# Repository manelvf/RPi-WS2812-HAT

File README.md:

# RPi-WS2812-HAT
WS2812B intelligent RGB-LED 8x8 Matrix HAT (Hardware Attached on Top) for Raspberry Pi.

## Shop
* [RPi-WS2812-HAT](http://www.watterott.com/en/RPi-WS2812-HAT)

## Features
* 64 WS2812 RGB-LED with built-in controller with serial interface
* Atmel ATtiny85 with [Micronucleus](https://github.com/micronucleus/micronucleus) USB Bootloader
* MicroUSB connector
* ID EEPROM
* [Raspberry Pi HAT](https://github.com/raspberrypi/hats) compatible

## Hardware and Software
* [Schematics + Layout](https://github.com/watterott/RPi-WS2812-HAT/tree/master/pcb)
* [Arduino and Raspberry Pi Examples](https://github.com/watterott/RPi-WS2812-HAT/tree/master/src)
* [Little Wire](http://littlewire.cc) can also be used on the ATtiny85.
* [FAQ (Frequently Asked Questions)](https://github.com/watterott/RPi-WS2812-HAT/blob/master/docu/FAQ.md)

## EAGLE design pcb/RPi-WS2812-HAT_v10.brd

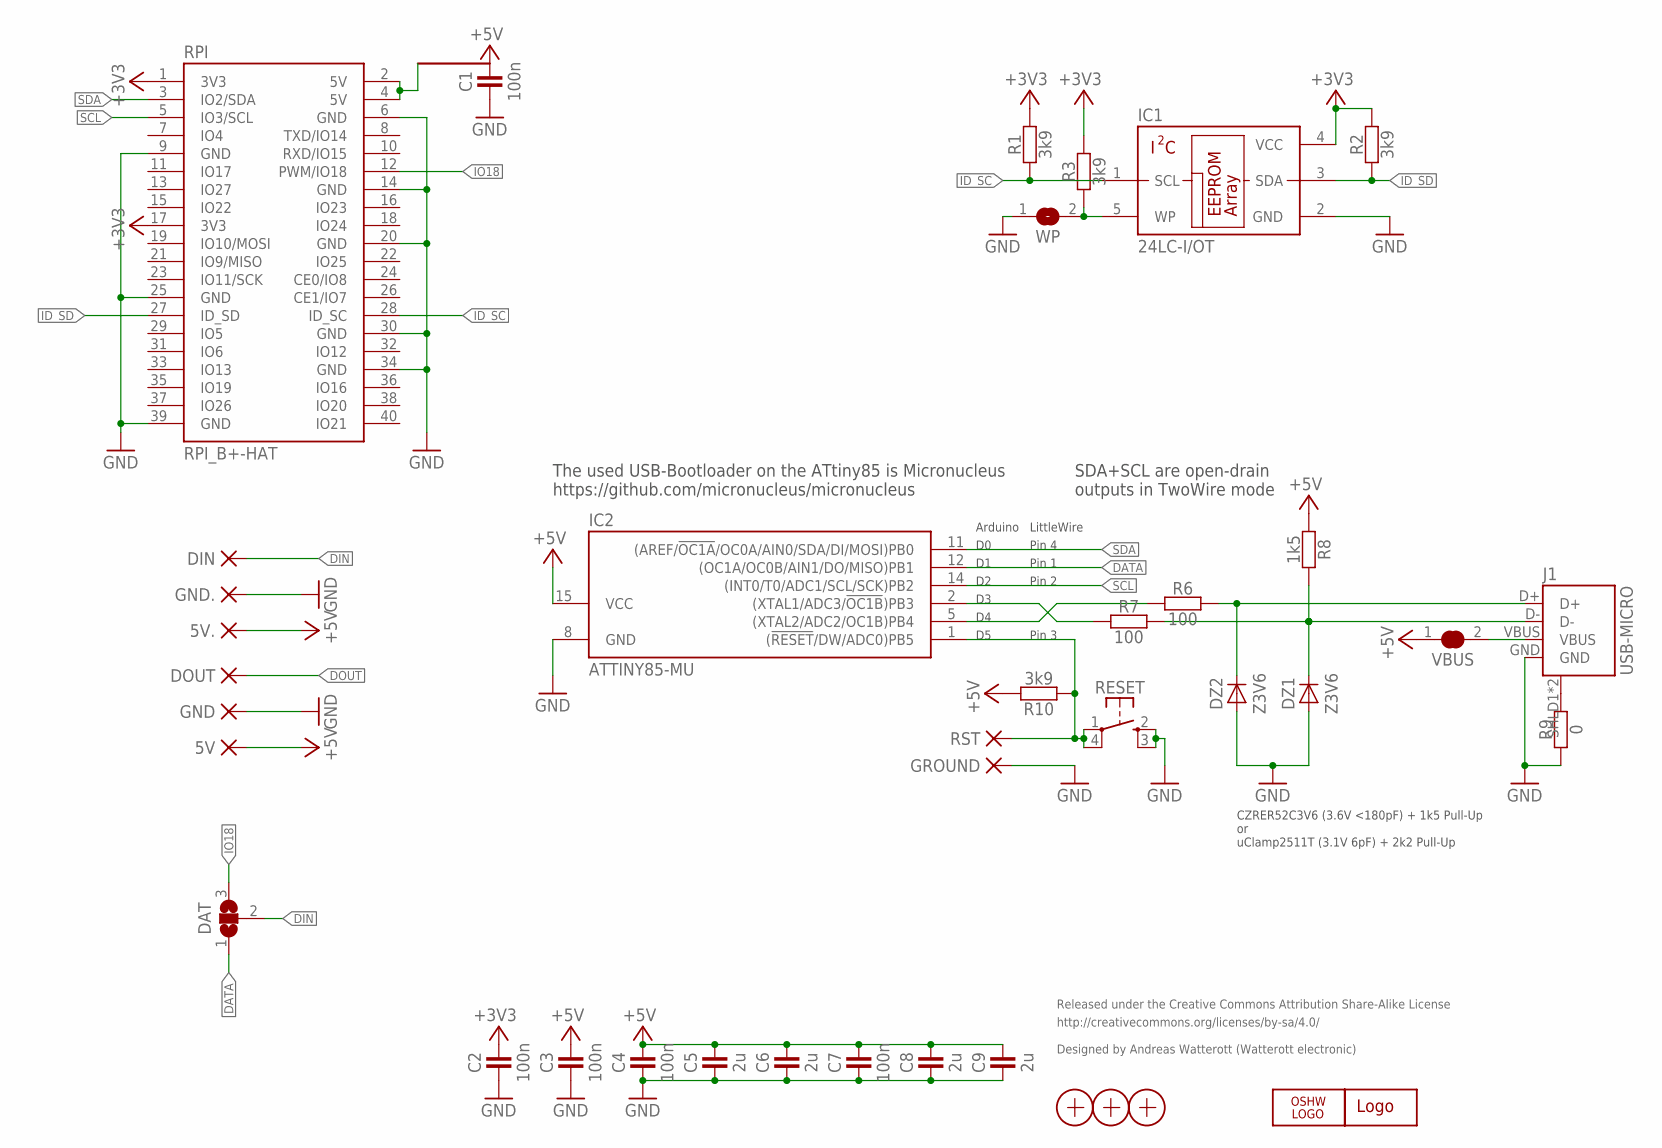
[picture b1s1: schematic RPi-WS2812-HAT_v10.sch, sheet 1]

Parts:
5V, 5V.: PAD-1.27X2.54_NC
C1, C2, C3, C4, C7: 100n; R0402
C5, C6, C8, C9: 2u; R0402
DAT: JUMPER3-0603
DIN: PAD-1.27X2.54_NC
DOUT: PAD-1.27X2.54_NC
DZ1, DZ2: Z3V6; SOD882
GND, GND.: PAD-1.27X2.54_NC
GROUND: PAD-1.27X1.27_NC
IC1: 24LC-I/OT; SOT23-5
IC2: ATTINY85-MU; QFN20-PAD
J1: USB-MICRO; USB-MICRO-10103594
LOGO1: LOGO-S_PLACE_S; SPARK_TPLACE_S
LOGO2: OSHW_LOGOX0070; OSHW_6X70
R1, R2, R3, R10: 3k9; R0402
R6, R7: 100; R0402
R8: 1k5; R0402
R9: 0; R0402
RESET: SW-TACTILE-TL3315; SW_TL3315N
RPI: RPI_B+-HAT; RPI-B+HAT
RST: PAD-1.27X1.27_NC
VBUS: JUMPER2-0603-NC; JUMPER2-0603_NC
WP: JUMPER2-0603-NC; JUMPER2-0603_NC
X1, X2, X3: PASSER-07; PASSER_07MM

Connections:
5V: RPI.2 (5V), RPI.4 (5V)
+3V3: C2.2, IC1.4 (VCC), R1.2, R2.2, R3.2, RPI.1 (3V3), RPI.17 (3V3)
+5V: 5V.1, 5V..1, C1.2, C3.2, C4.2, C5.2, C6.2, C7.2, C8.2, C9.2, IC2.15 (VCC), R8.1, R10.2, VBUS.1; also elsewhere on the board
D2_N: IC2.2 ((XTAL1/ADC3/!OC1B!)PB3), R7.1
D2_P: IC2.5 ((XTAL2/ADC2/OC1B)PB4), R6.1
DATA: DAT.1, IC2.12 ((OC1A/OC0B/AIN1/DO/MISO)PB1)
DIN: DAT.2, DIN.1; also elsewhere on the board
DOUT: DOUT.1; also elsewhere on the board
D_N: DZ1.C, J1.D-, R7.2, R8.2
D_P: DZ2.C, J1.D+, R6.2
GND: C1.1, C2.1, C3.1, C4.1, C5.1, C6.1, C7.1, C8.1, C9.1, DZ1.A, DZ2.A, GND.1, GND..1, GROUND.1, IC1.2 (GND), IC2.8 (GND), J1.GND, R9.1, RESET.2 (S1), RESET.3 (S2), RPI.6 (GND), RPI.9 (GND), RPI.14 (GND), RPI.20 (GND), RPI.25 (GND), RPI.30 (GND), RPI.34 (GND), RPI.39 (GND), WP.1; also elsewhere on the board
ID_SC: IC1.1 (SCL), R1.1, RPI.28 (ID_SC)
ID_SD: IC1.3 (SDA), R2.1, RPI.27 (ID_SD)
IO18: DAT.3, RPI.12 (PWM/IO18)
unnamed: J1.SHLD1 (SHIELD), J1.SHLD2 (SHIELD), R9.2
RST: IC2.1 ((!RESET!/DW/ADC0)PB5), R10.1, RESET.1, RESET.4 (P2), RST.1
SCL: IC2.14 ((INT0/T0/ADC1/SCL/SCK)PB2), RPI.5 (IO3/SCL)
SDA: IC2.11 ((AREF/!OC1A!/OC0A/AIN0/SDA/DI/MOSI)PB0), RPI.3 (IO2/SDA)
VBUS: J1.VBUS, VBUS.2
WP: IC1.5 (WP), R3.1, WP.2

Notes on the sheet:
Released under the Creative Commons Attribution Share-Alike License
http://creativecommons.org/licenses/by-sa/4.0/
Designed by Andreas Watterott (Watterott electronic)
The used USB-Bootloader on the ATtiny85 is Micronucleus https://github.com/micronucleus/micronucleus
CZRER52C3V6 (3.6V <180pF) + 1k5 Pull-Up or uClamp2511T (3.1V 6pF) + 2k2 Pull-Up
Pin 1
Pin 4
Pin 2
Pin 3
LittleWire
Arduino
SDA+SCL are open-drain outputs in TwoWire mode

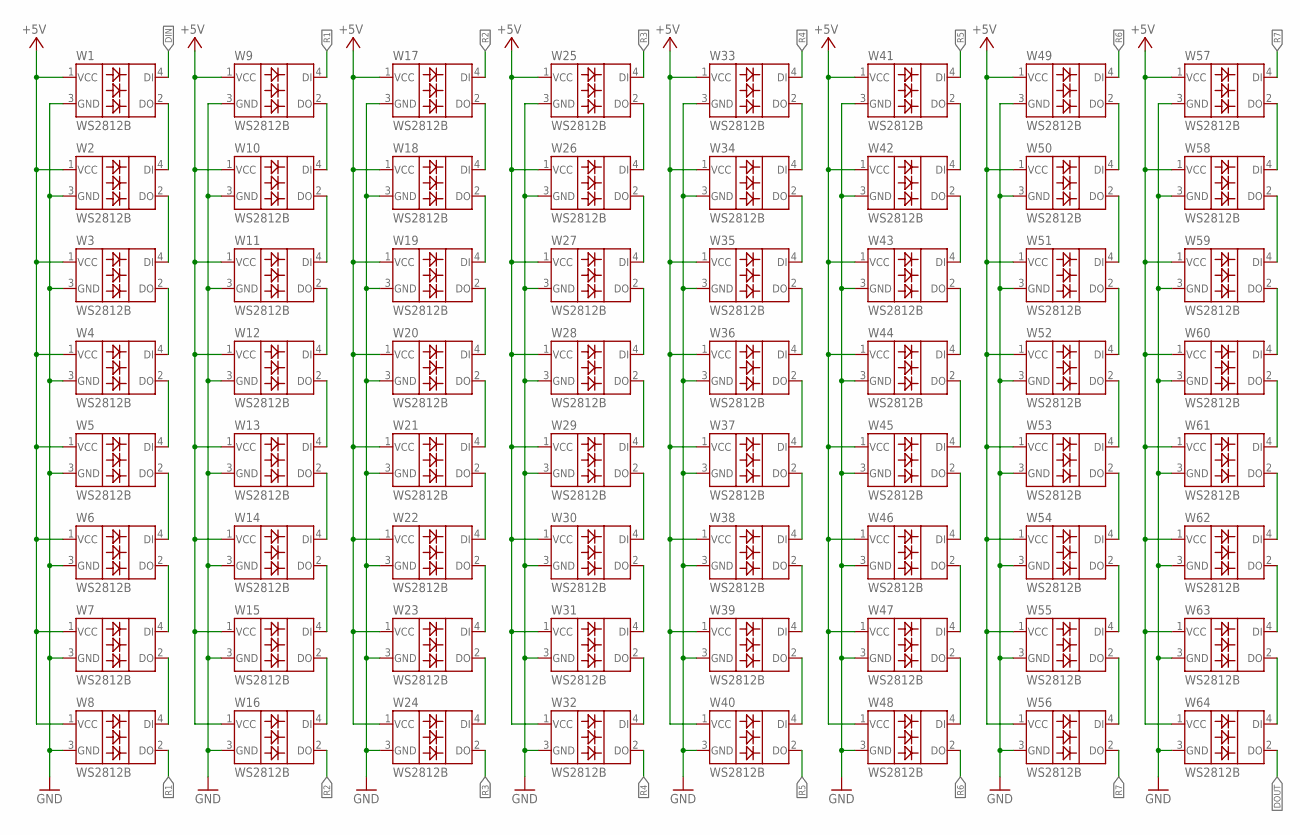
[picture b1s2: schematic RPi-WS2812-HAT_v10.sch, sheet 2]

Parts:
W1, W2, W3, W4, W5, W6, W7, W8, W9, W10, W11, W12, W13, W14, W15, W16, W17, W18, W19, W20, W21, W22, W23, W24, W25, W26, W27, W28, W29, W30, W31, W32, W33, W34, W35, W36, W37, W38, W39, W40, W41, W42, W43, W44, W45, W46, W47, W48, W49, W50, W51, W52, W53, W54, W55, W56, W57, W58, W59, W60, W61, W62, W63, W64: WS2812B

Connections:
+5V: W1.1 (VCC), W2.1 (VCC), W3.1 (VCC), W4.1 (VCC), W5.1 (VCC), W6.1 (VCC), W7.1 (VCC), W8.1 (VCC), W9.1 (VCC), W10.1 (VCC), W11.1 (VCC), W12.1 (VCC), W13.1 (VCC), W14.1 (VCC), W15.1 (VCC), W16.1 (VCC), W17.1 (VCC), W18.1 (VCC), W19.1 (VCC), W20.1 (VCC), W21.1 (VCC), W22.1 (VCC), W23.1 (VCC), W24.1 (VCC), W25.1 (VCC), W26.1 (VCC), W27.1 (VCC), W28.1 (VCC), W29.1 (VCC), W30.1 (VCC), W31.1 (VCC), W32.1 (VCC), W33.1 (VCC), W34.1 (VCC), W35.1 (VCC), W36.1 (VCC), W37.1 (VCC), W38.1 (VCC), W39.1 (VCC), W40.1 (VCC), W41.1 (VCC), W42.1 (VCC), W43.1 (VCC), W44.1 (VCC), W45.1 (VCC), W46.1 (VCC), W47.1 (VCC), W48.1 (VCC), W49.1 (VCC), W50.1 (VCC), W51.1 (VCC), W52.1 (VCC), W53.1 (VCC), W54.1 (VCC), W55.1 (VCC), W56.1 (VCC), W57.1 (VCC), W58.1 (VCC), W59.1 (VCC), W60.1 (VCC), W61.1 (VCC), W62.1 (VCC), W63.1 (VCC), W64.1 (VCC); also elsewhere on the board
DIN: W1.4 (DI); also elsewhere on the board
DOUT: W64.2 (DO); also elsewhere on the board
GND: W1.3 (GND), W2.3 (GND), W3.3 (GND), W4.3 (GND), W5.3 (GND), W6.3 (GND), W7.3 (GND), W8.3 (GND), W9.3 (GND), W10.3 (GND), W11.3 (GND), W12.3 (GND), W13.3 (GND), W14.3 (GND), W15.3 (GND), W16.3 (GND), W17.3 (GND), W18.3 (GND), W19.3 (GND), W20.3 (GND), W21.3 (GND), W22.3 (GND), W23.3 (GND), W24.3 (GND), W25.3 (GND), W26.3 (GND), W27.3 (GND), W28.3 (GND), W29.3 (GND), W30.3 (GND), W31.3 (GND), W32.3 (GND), W33.3 (GND), W34.3 (GND), W35.3 (GND), W36.3 (GND), W37.3 (GND), W38.3 (GND), W39.3 (GND), W40.3 (GND), W41.3 (GND), W42.3 (GND), W43.3 (GND), W44.3 (GND), W45.3 (GND), W46.3 (GND), W47.3 (GND), W48.3 (GND), W49.3 (GND), W50.3 (GND), W51.3 (GND), W52.3 (GND), W53.3 (GND), W54.3 (GND), W55.3 (GND), W56.3 (GND), W57.3 (GND), W58.3 (GND), W59.3 (GND), W60.3 (GND), W61.3 (GND), W62.3 (GND), W63.3 (GND), W64.3 (GND); also elsewhere on the board
unnamed: W1.2 (DO), W2.4 (DI)
unnamed: W2.2 (DO), W3.4 (DI)
unnamed: W3.2 (DO), W4.4 (DI)
unnamed: W4.2 (DO), W5.4 (DI)
unnamed: W5.2 (DO), W6.4 (DI)
unnamed: W6.2 (DO), W7.4 (DI)
unnamed: W7.2 (DO), W8.4 (DI)
unnamed: W9.2 (DO), W10.4 (DI)
unnamed: W10.2 (DO), W11.4 (DI)
unnamed: W11.2 (DO), W12.4 (DI)
unnamed: W12.2 (DO), W13.4 (DI)
unnamed: W13.2 (DO), W14.4 (DI)
unnamed: W15.2 (DO), W16.4 (DI)
unnamed: W14.2 (DO), W15.4 (DI)
unnamed: W23.2 (DO), W24.4 (DI)
unnamed: W22.2 (DO), W23.4 (DI)
unnamed: W21.2 (DO), W22.4 (DI)
unnamed: W20.2 (DO), W21.4 (DI)
unnamed: W19.2 (DO), W20.4 (DI)
unnamed: W18.2 (DO), W19.4 (DI)
unnamed: W17.2 (DO), W18.4 (DI)
unnamed: W25.2 (DO), W26.4 (DI)
unnamed: W26.2 (DO), W27.4 (DI)
unnamed: W28.2 (DO), W29.4 (DI)
unnamed: W27.2 (DO), W28.4 (DI)
unnamed: W29.2 (DO), W30.4 (DI)
unnamed: W31.2 (DO), W32.4 (DI)
unnamed: W30.2 (DO), W31.4 (DI)
unnamed: W55.2 (DO), W56.4 (DI)
unnamed: W41.2 (DO), W42.4 (DI)
unnamed: W33.2 (DO), W34.4 (DI)
unnamed: W34.2 (DO), W35.4 (DI)
unnamed: W42.2 (DO), W43.4 (DI)
unnamed: W43.2 (DO), W44.4 (DI)
unnamed: W35.2 (DO), W36.4 (DI)
unnamed: W36.2 (DO), W37.4 (DI)
unnamed: W37.2 (DO), W38.4 (DI)
unnamed: W39.2 (DO), W40.4 (DI)
unnamed: W47.2 (DO), W48.4 (DI)
unnamed: W46.2 (DO), W47.4 (DI)
unnamed: W54.2 (DO), W55.4 (DI)
unnamed: W38.2 (DO), W39.4 (DI)
unnamed: W45.2 (DO), W46.4 (DI)
unnamed: W44.2 (DO), W45.4 (DI)
unnamed: W52.2 (DO), W53.4 (DI)
unnamed: W53.2 (DO), W54.4 (DI)
unnamed: W51.2 (DO), W52.4 (DI)
unnamed: W50.2 (DO), W51.4 (DI)
unnamed: W49.2 (DO), W50.4 (DI)
unnamed: W63.2 (DO), W64.4 (DI)
unnamed: W62.2 (DO), W63.4 (DI)
unnamed: W61.2 (DO), W62.4 (DI)
unnamed: W60.2 (DO), W61.4 (DI)
unnamed: W59.2 (DO), W60.4 (DI)
unnamed: W57.2 (DO), W58.4 (DI)
unnamed: W58.2 (DO), W59.4 (DI)
R1: W8.2 (DO), W9.4 (DI)
R2: W16.2 (DO), W17.4 (DI)
R3: W24.2 (DO), W25.4 (DI)
R4: W32.2 (DO), W33.4 (DI)
R5: W40.2 (DO), W41.4 (DI)
R6: W48.2 (DO), W49.4 (DI)
R7: W56.2 (DO), W57.4 (DI)

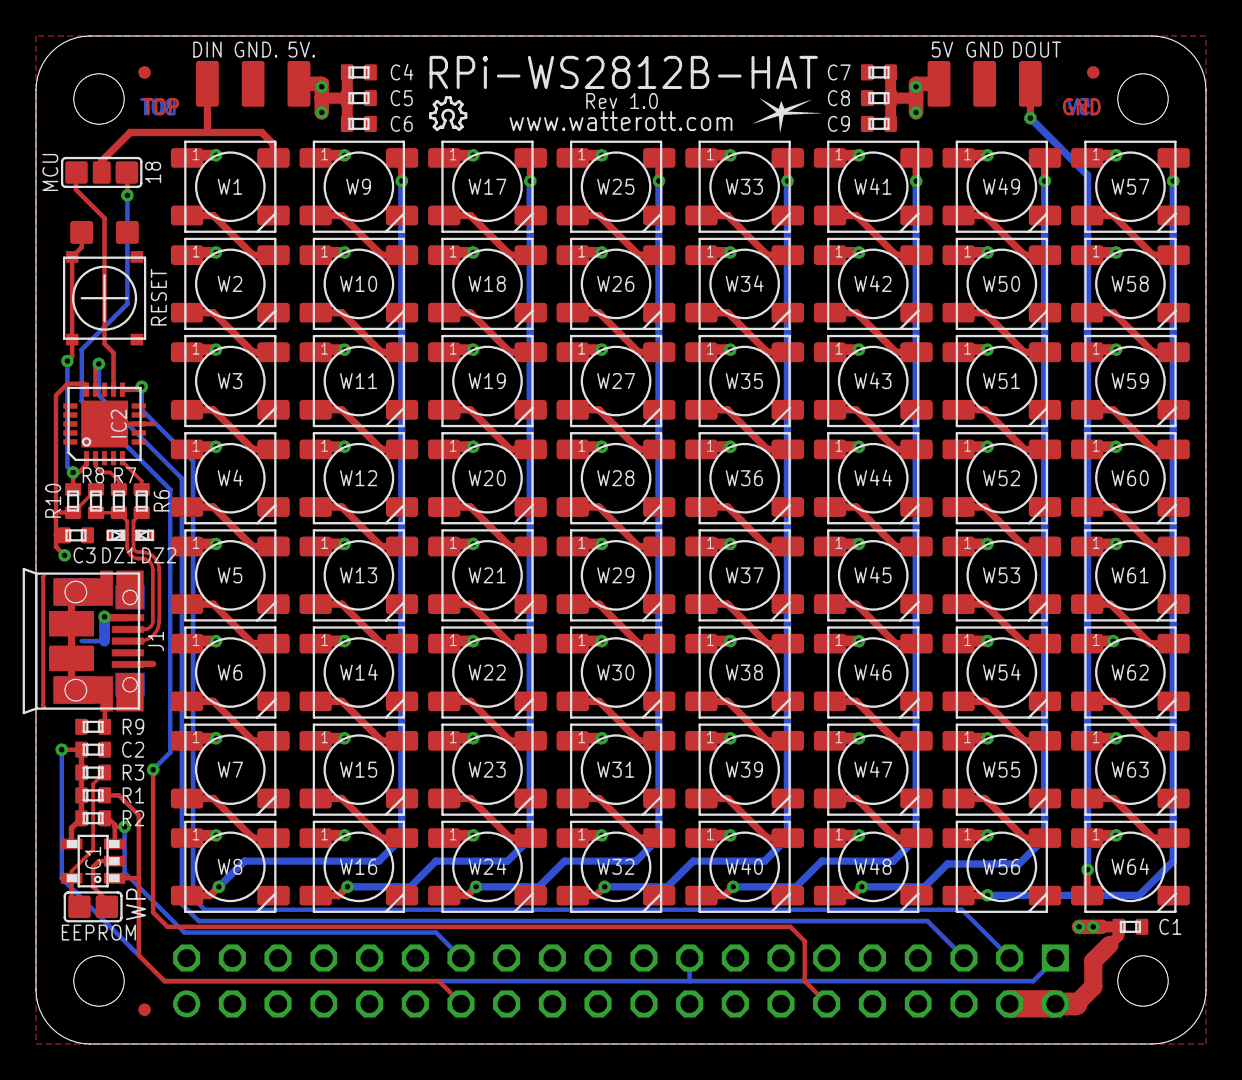
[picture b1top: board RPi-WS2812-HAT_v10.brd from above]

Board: 2 copper layers, 65.0 x 56.0 mm, 104 parts (1 on the bottom side), 83 nets.

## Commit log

2014-09-16 added readme
2014-09-25 added image
2015-01-01 added layout and schematics
2015-01-01 added docu
2015-01-01 added examples
2015-01-02 updated docu
2015-01-02 updated image
2015-01-02 updated examples
2015-01-08 updated layout
2015-01-11 moved image
2015-02-03 updated schematics
2015-03-01 New example: text with scroll
